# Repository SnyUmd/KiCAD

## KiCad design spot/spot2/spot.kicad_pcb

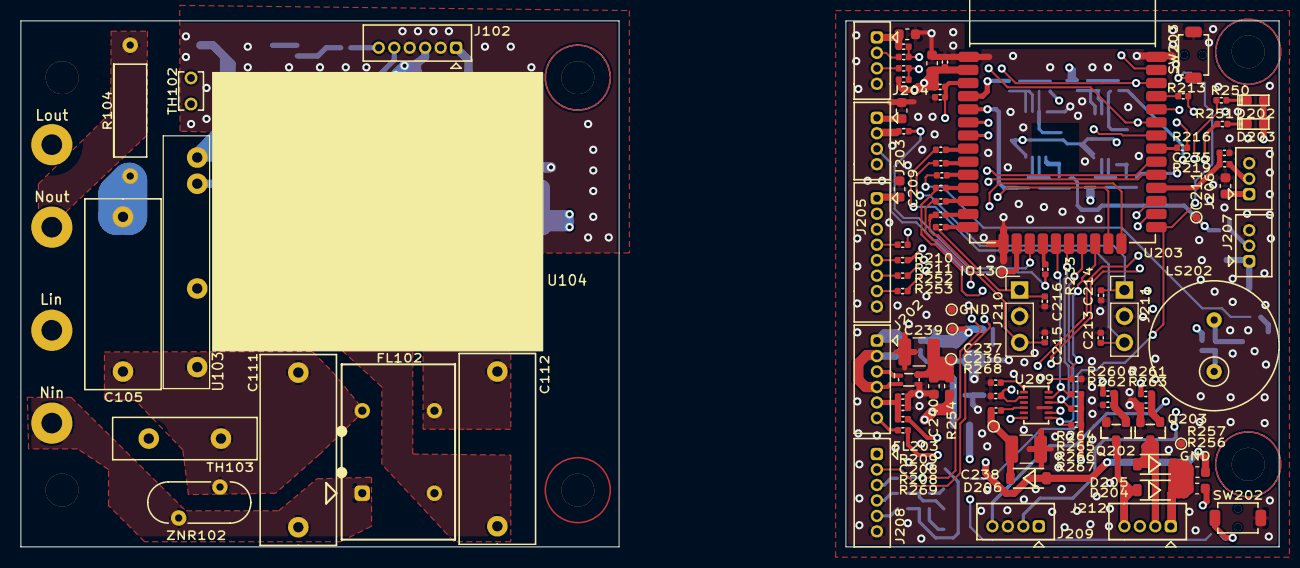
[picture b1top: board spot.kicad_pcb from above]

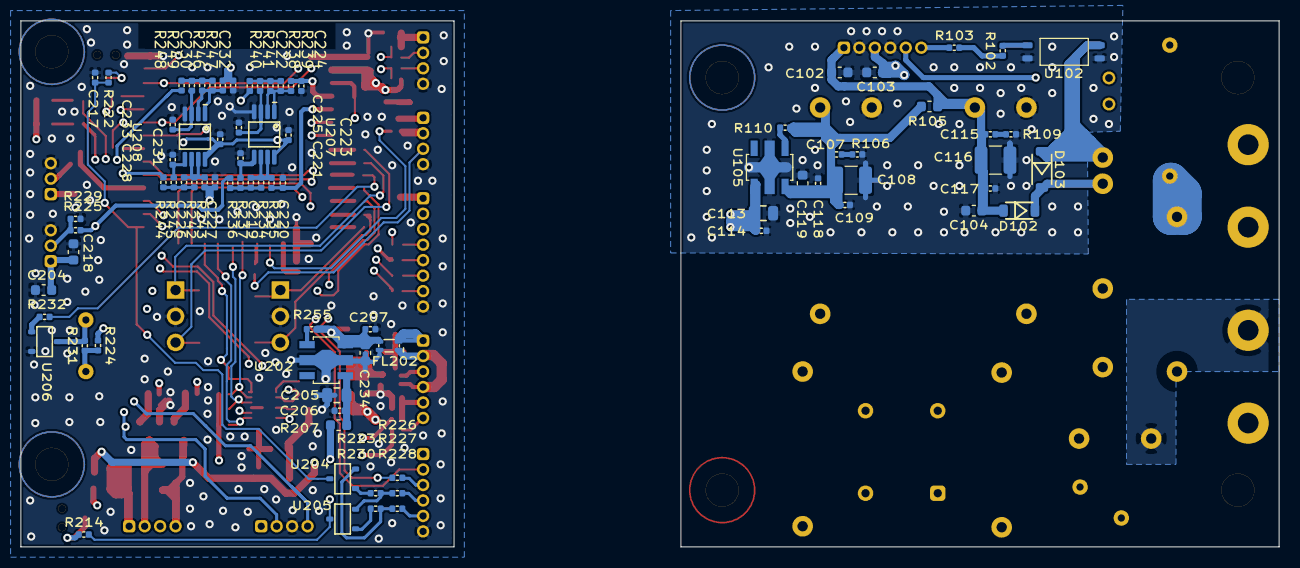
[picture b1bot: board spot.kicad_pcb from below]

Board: 4 copper layers, 122.0 x 51.0 mm, 189 parts (81 on the bottom side), 122 nets.

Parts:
C102, C103: 10uF/10V; C_0603_1608Metric
C104: 10u/10V; C_0603_1608Metric
C105, C111: 1uF/450V; ECQE2105KF
C107, C115, C213, C214, C215, C216: NC; C_0402_1005Metric
C108, C116: 1uF; C_1210_3225Metric
C109, C117: 1uF; C_0402_1005Metric
C112: 1uF/270V; ECQE2105KF
C113, C205: 2.2u; C_0805_2012Metric
C114, C118, C206, C207: 0.1u; C_0402_1005Metric
C119, C234: 0.33u; C_0603_1608Metric
C202, C203, C204, C209, C211, C218, C229, C240: 10u; C_0603_1608Metric
C208, C231: 1u; C_0402_1005Metric
C210, C212, C217, C219, C220, C221, C222, C223, C224, C225, C226, C227, C228, C230, C232, C233, C235, C236, C237: C_Small; C_0402_1005Metric
C238, C239: 47u; C_1210_3225Metric
D102: RB160M-30TR; RB168M-40TR
D103: NC(GS1010FL); GS1010FL
D202, D203: LED; LED1608
D204, D205, D206: GS1010FL
FL102: SU9VD-10020
FL202, FL203: EMI_Filter_CommonMode; ACM2012-900-2P-T
Hole101, Hole102, Hole103, Hole104, Hole201, Hole202: Hole3.2
J102, J202, J208: Conn_01x06; ZH_B6B-ZR
J203, J204, J209, J212: Conn_01x04; ZH_B4B-ZR
J205: Conn_01x08; ZH_B8B-ZR
J206, J207: Conn_01x03; ZH_B3B-ZR
J210, J211: Conn_01x03; PinHeader_1x03_P2.54mm_Vertical
LS202: PKM13EPYH4000-A0
P102, P103: AC_L; AC-TP
P104, P105: AC_N; AC-TP
P203, P204, P205, P208, P209, P210: TP; TP0.5
Q202, Q203: IRLML6344TRPBFTR
R102: 220; C_0402_1005Metric
R103, R205, R206, R210, R211, R213, R214, R216, R219, R222, R225, R226, R227, R228, R233, R252, R253, R258, R259: 100; C_0402_1005Metric
R104: NC; CFS50J1MB
R105: NC; C_0603_1608Metric
R106, R109: NC; C_0402_1005Metric
R110, R209, R223, R229, R230, R255: 10k; C_0402_1005Metric
R202, R203, R260, R261, R264, R265, R266, R267: 4.7k; C_0402_1005Metric
R204, R212, R234, R235, R236, R237, R238, R239, R240, R241, R242, R243, R244, R245, R246, R247, R248, R249, R269: R; C_0402_1005Metric
R207, R254, R256, R257: R; C_0603_1608Metric
R208: 1k; C_0402_1005Metric
R215, R217, R218, R220, R221, R224, R231, R232: 0; C_0402_1005Metric
R250, R251: 2.2k; C_0402_1005Metric
R262, R263: 100k; C_0402_1005Metric
R268: 1M; C_0402_1005Metric
SW202, SW203: SW_Push; TVAF06-A020B-R
TH102: 103AT-2
TH103: MF-RM055-240-0
TP202: TestPoint; TP0.5
U102: TLP291
U103: AQG12205
U104: 47252
U105, U202: NJM2884U1-33-TE1
U203: ESP32-WROOM-32; ESP32-WROOM-32D
U204, U205, U206: 2SC2712-Y
U207: MCP6002-xSN; MCP6002-I-MS
U208: MCP6002-I-MS
U209: RX-8035
ZNR102: TSV07D271KR

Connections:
+3.3VP: C103.1, C113.1, C114.1, J102.3, TH102.2, U105.4
+3V3: C202.2, C203.2, C204.2, C209.2, C210.1, C211.2, C218.2, C223.1, C229.1, C231.1, C236.1, D202.2, D203.2, J203.1, J204.1, J205.1, J206.1, J207.1, J208.1, J209.1, R202.2, R203.2, R207.1, R212.2, R224.1, R254.1, R256.1, R265.1, R266.1, R267.1, U203.2, U207.8, U208.8, U209.2
+5P: FL202.3, J202.1
+5V: C102.1, C104.1, C115.1, C116.1, C117.1, D102.A, J102.1, R105.1, U104.7
+5VP: C207.1, C234.1, D206.A, FL202.4, P205.1, R255.1, R257.1, U202.5
Buzzer: R218.1, R232.2
EN: C212.1, R212.1, R214.2, U203.3, U205.3
GND: C102.2, C103.2, C104.2, C108.2, C109.2, C113.2, C114.2, C116.2, C117.2, C118.2, C119.2, J102.2, J102.4, R106.1, R109.1, U102.2, U102.3, U104.6, U104.9, U105.2
GND1: C202.1, C203.1, C204.1, C205.2, C206.2, C207.2, C208.2, C209.1, C210.2, C211.1, C212.2, C213.2, C214.2, C215.2, C216.2, C217.2, C218.1, C220.2, C221.2, C223.2, C224.2, C225.2, C227.2, C228.2, C229.2, C231.2, C232.2, C233.2, C234.2, C235.2, C236.2, C237.2, C238.1, C239.1, C240.1, FL202.2, FL203.4, J203.4, J204.4, J205.8, J206.3, J207.3, J208.6, J209.3, J210.2, J211.2, P208.1, P210.1, Q202.2, Q203.2, R209.2, R229.1, R262.1, R263.1, R264.2, SW202.1, SW203.1, U202.2, U203.1, U203.15, U203.38, U206.2, U207.4, U208.4, U209.9
GNDS: FL202.1, FL203.3, J202.2, J202.4
HumanSensor_in: C235.1, R219.1, U203.28
IO_0: C217.1, R222.2, U203.25, U204.3
IlluminanceSensor_in: R225.1, R236.1, TP202.1
Morter0: R258.1, R261.1
Morter1: R259.1, R260.1
unnamed: C105.1, R104.2
unnamed: C105.2, C111.2, FL102.3, TH103.1, U103.4, ZNR102.2
unnamed: C107.1, C108.1, C109.1, C118.1, C119.1, R105.2, R110.1, U104.10, U105.5
unnamed: C107.2, R106.2
unnamed: C111.1, FL102.1, P104.1, P105.1, R104.1, ZNR102.1
unnamed: C112.1, FL102.2, U104.5
unnamed: C112.2, FL102.4, U104.1
unnamed: C115.2, R109.2
unnamed: C205.1, C206.1, R207.2, U202.4
unnamed: C208.1, J202.5, R208.2, R209.1
unnamed: C219.1, R234.1, R235.1, U207.6, U207.7
unnamed: C219.2, R234.2, R236.2, R237.1
unnamed: C221.1, R237.2, U207.5
unnamed: C222.1, R238.1, R239.1, U207.1, U207.2
unnamed: C222.2, R238.2, R240.2, R241.1
unnamed: C225.1, R241.2, U207.3
unnamed: C226.1, R242.1, R243.1, U208.6, U208.7
unnamed: C226.2, R242.2, R244.2, R245.1
unnamed: C228.1, R245.2, U208.5
unnamed: C230.1, R246.1, R247.1, U208.1, U208.2
unnamed: C230.2, R246.2, R248.2, R249.1
unnamed: C233.1, R249.2, U208.3
unnamed: C237.1, U209.1
unnamed: C238.2, D206.K, P209.1, R268.2
unnamed: C239.2, C240.2, FL203.2, P204.1, R254.2
unnamed: D102.K, D103.K, U103.2
unnamed: D103.A, U102.4, U103.1
unnamed: D202.1, R250.2
unnamed: D203.1, R251.2
unnamed: D204.A, J212.4, Q202.3
unnamed: D204.K, D205.K, J212.1, J212.3, R256.2, R257.2
unnamed: D205.A, J212.2, Q203.3
unnamed: FL203.1, J202.3
unnamed: J102.5, TH102.1
unnamed: J102.6, R103.1
unnamed: J202.6, R269.2
unnamed: J203.2, R204.2
unnamed: J204.2, R205.2
unnamed: J204.3, R206.2
unnamed: J205.4, R210.2
unnamed: J205.5, R211.2
unnamed: J205.6, R252.2
unnamed: J205.7, R253.2
unnamed: J206.2, R219.2
unnamed: J207.2, R225.2, R229.2
unnamed: J208.3, R226.2
unnamed: J208.4, R227.2
unnamed: J208.5, R228.2
unnamed: LS202.1, R224.2, R231.1
unnamed: LS202.2, R231.2, U206.3
unnamed: P102.1, TH103.2
unnamed: P103.1, U103.3
unnamed: P203.1, U203.16
unnamed: Q202.1, R260.2, R262.2
unnamed: Q203.1, R261.2, R263.2
unnamed: R102.2, U102.1
unnamed: R110.2, U105.1
unnamed: R213.1, U203.35
unnamed: R214.1, SW202.2
unnamed: R215.2, U203.8
unnamed: R216.1, U203.31
unnamed: R217.2, U203.9
unnamed: R218.2, U203.10
unnamed: R220.2, U203.13
unnamed: R221.2, U203.14
unnamed: R222.1, SW203.2
unnamed: R223.1, U204.1
unnamed: R223.2, R227.1, U205.2
unnamed: R228.1, R230.2, U204.2
unnamed: R230.1, U205.1
unnamed: R232.1, U206.1
unnamed: R233.2, U203.18
unnamed: R250.1, U203.27
unnamed: R251.1, U203.26
unnamed: R255.2, U202.1
unnamed: R258.2, U203.11
unnamed: R259.2, U203.12
unnamed: R268.1, U209.4
RTC_Event1: R264.1, U203.22, U209.12
RTC_INTA: R266.2, U203.20, U209.10
RTC_INTB: R267.2, U203.21, U209.7
RTC_RESout: R265.2, U203.19, U209.11
RXD0: R226.1, U203.34
RXD1: R204.1, U203.17
RelayCtrl_0: R102.1, R103.2
RelayCtrl_1: R269.1, U203.32
SCL: R202.1, R205.1, U203.36, U209.6
SDA: R203.1, R206.1, U203.33, U209.8
SPI_CS0: R211.1, U203.29
SPI_CS1: R252.1, U203.23
SPI_CS2: R253.1, U203.24
SPI_MISO: R210.1, U203.30
SPI_MOSI: J205.3, U203.37
SPI_SCK: J205.2, R216.2
Senser0out: C224.1, R239.2, U203.4
Senser1out: C220.1, R235.2, U203.5
Senser2in: J209.2, R248.1
Senser2out: C232.1, R247.2, U203.6
Senser3in: J209.4, R244.1
Senser3out: C227.1, R243.2, U203.7
TXD0: J208.2, R213.2
TXD1: J203.3, R233.1
Thermistor_in: R208.1, R240.1
Touch5: C216.1, J210.1, R221.1
Touch6: C215.1, J210.3, R220.1
Touch8: C214.1, J211.1, R217.1
Touch9: C213.1, J211.3, R215.1

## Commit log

2022-09-21 初回コミット
2022-09-27 no message
2022-09-27 着信お知らせプロジェクト作成
2023-09-11 ブザー部、I2C部完了
2023-09-12 ブザーを別タスクに
